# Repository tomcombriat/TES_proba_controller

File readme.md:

## MIDI controller using probabilities

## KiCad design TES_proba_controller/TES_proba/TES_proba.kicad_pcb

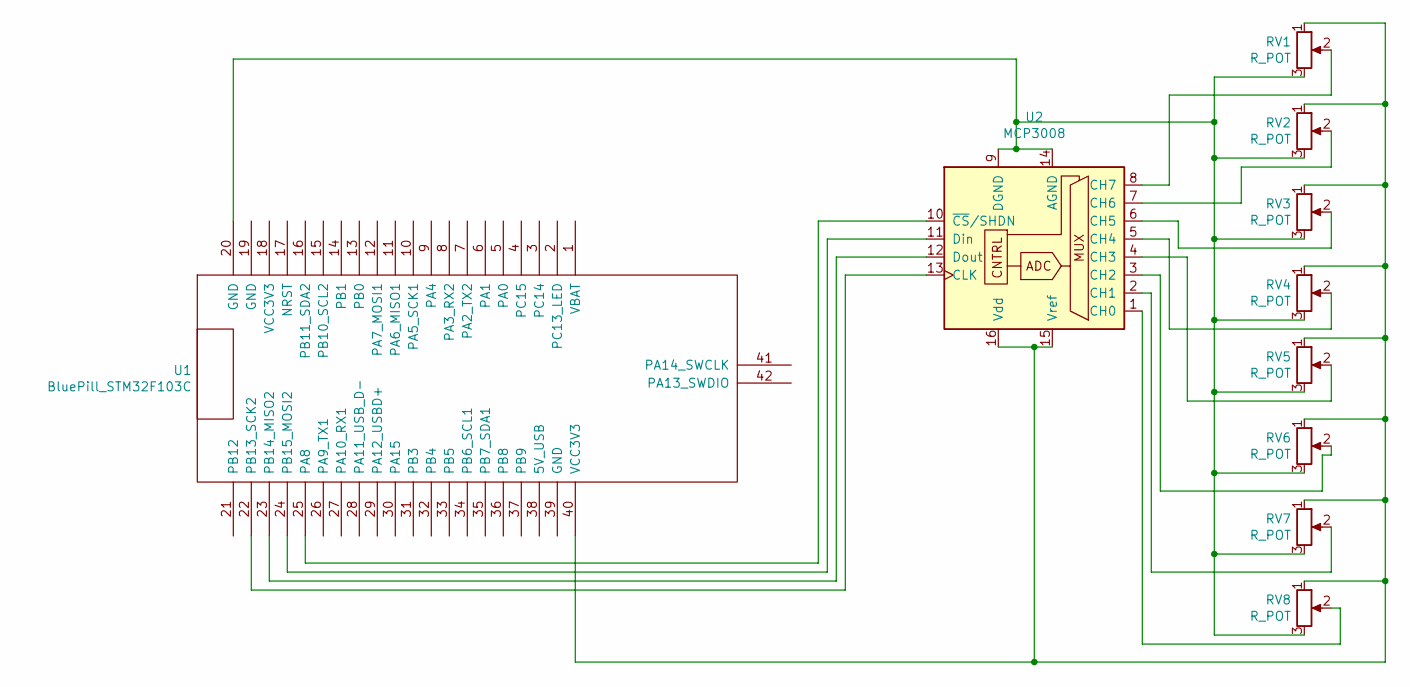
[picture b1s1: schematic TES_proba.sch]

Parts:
RV1, RV2, RV3, RV4, RV5, RV6, RV7, RV8: R_POT; Potentiometer_Bourns_PTV09A-1_Single_Vertical
U1: BluePill_STM32F103C
U2: MCP3008; DIP-16_W7.62mm

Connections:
unnamed: RV1.1, RV2.1, RV3.1, RV4.1, RV5.1, RV6.1, RV7.1, RV8.1, U1.40 (VCC3V3), U2.15 (Vref), U2.16 (Vdd)
unnamed: RV1.2, U2.8 (CH7)
unnamed: RV1.3, RV2.3, RV3.3, RV4.3, RV5.3, RV6.3, RV7.3, RV8.3, U1.20 (GND), U2.9 (DGND), U2.14 (AGND)
unnamed: RV2.2, U2.7 (CH6)
unnamed: RV3.2, U2.6 (CH5)
unnamed: RV4.2, U2.5 (CH4)
unnamed: RV5.2, U2.4 (CH3)
unnamed: RV6.2, U2.3 (CH2)
unnamed: RV7.2, U2.2 (CH1)
unnamed: RV8.2, U2.1 (CH0)
unnamed: U1.22 (PB13_SCK2), U2.13 (CLK)
unnamed: U1.23 (PB14_MISO2), U2.12 (Dout)
unnamed: U1.24 (PB15_MOSI2), U2.11 (Din)
unnamed: U1.25 (PA8), U2.10 (~CS~/SHDN)

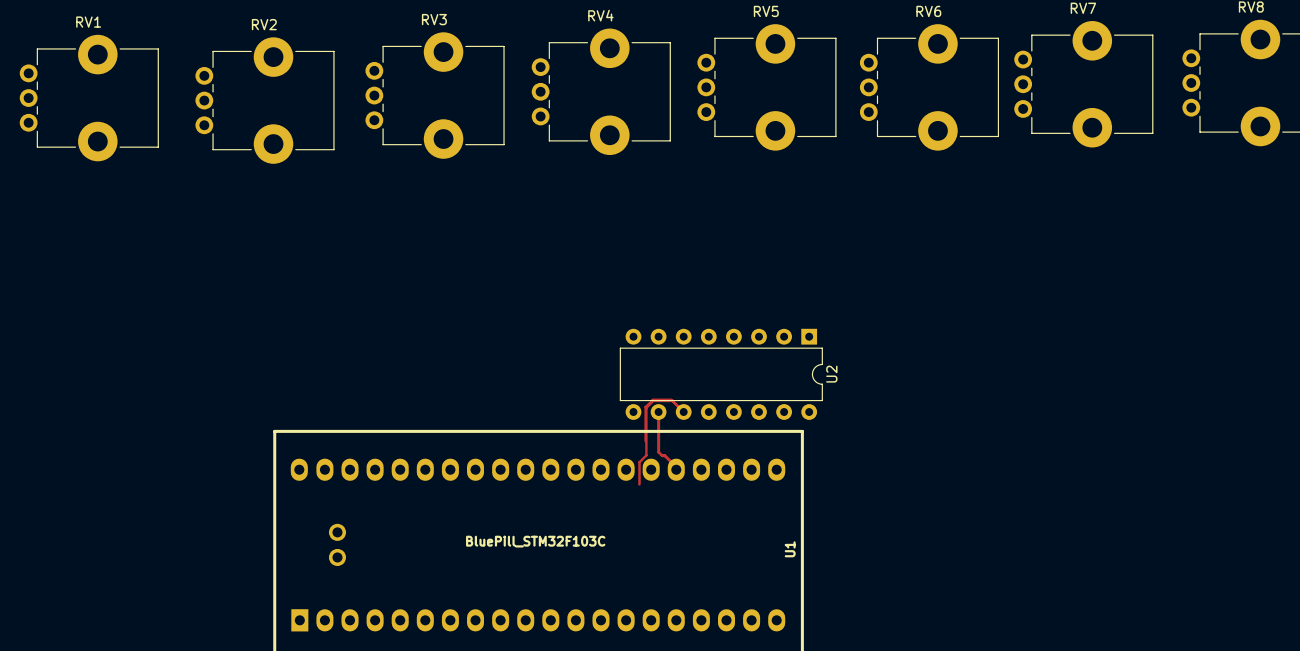
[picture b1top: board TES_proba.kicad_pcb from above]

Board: 2 copper layers, 10 parts (0 on the bottom side), 14 nets.

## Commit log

2019-06-10 test
2019-06-10 Test: speed of MCP3008 with nodesign library: 40micros for a read
